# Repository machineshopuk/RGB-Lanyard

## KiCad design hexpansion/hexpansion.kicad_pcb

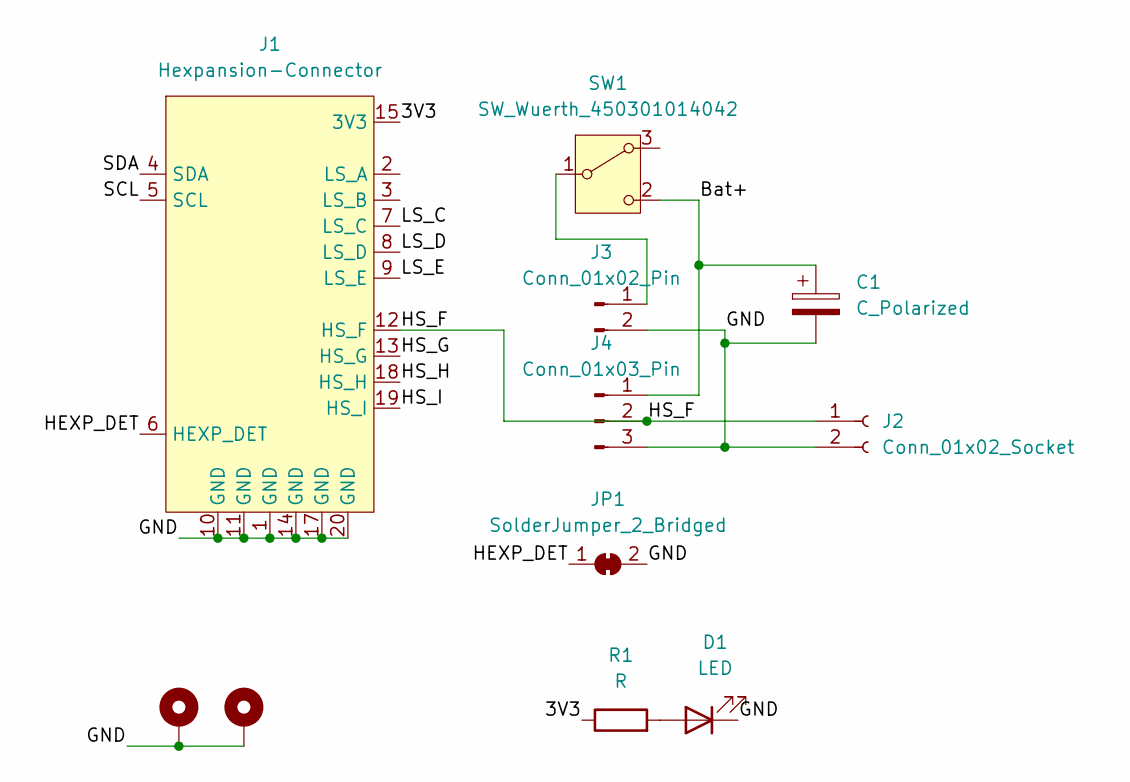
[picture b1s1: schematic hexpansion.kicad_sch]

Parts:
C1: C_Polarized; CP_Radial_D8.0mm_P3.50mm
D1: LED; LED_0805_2012Metric
H1, H2: MountingHole_Pad; MountingHole_2.2mm_M2_Pad_Via
J1: Hexpansion-Connector; hexpansion-edge-connector
J2: Conn_01x02_Socket; PinSocket_1x02_P2.54mm_Horizontal
J3: Conn_01x02_Pin; JST_XH_B2B-XH-A_1x02_P2.50mm_Vertical
J4: Conn_01x03_Pin; JST_XH_B3B-XH-A_1x03_P2.50mm_Vertical
JP1: SolderJumper_2_Bridged; SolderJumper-2_P1.3mm_Bridged_RoundedPad1.0x1.5mm
R1: R; R_0603_1608Metric
SW1: SW_Wuerth_450301014042; SW_Slide-03_Wuerth-WS-SLTV_10x2.5x6.4_P2.54mm

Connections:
/3V3: J1.15 (3V3), J1.16 (3V3), R1.1
/Bat+: C1.1, J4.1, SW1.2 (C)
/GND: C1.2, D1.1 (K), H1.1, H2.1, J1.1 (GND), J1.10 (GND), J1.11 (GND), J1.14 (GND), J1.17 (GND), J1.20 (GND), J2.2, J3.2, J4.3, JP1.2 (B)
/HEXP_DET: J1.6 (HEXP_DET), JP1.1 (A)
/HS_F: J1.12 (HS_F), J2.1, J4.2
/HS_G: J1.13 (HS_G)
/HS_H: J1.18 (HS_H)
/HS_I: J1.19 (HS_I)
/LS_C: J1.7 (LS_C)
/LS_D: J1.8 (LS_D)
/LS_E: J1.9 (LS_E)
/SCL: J1.5 (SCL)
/SDA: J1.4 (SDA)
unnamed: D1.2 (A), R1.2
unnamed: J3.1, SW1.1 (B)

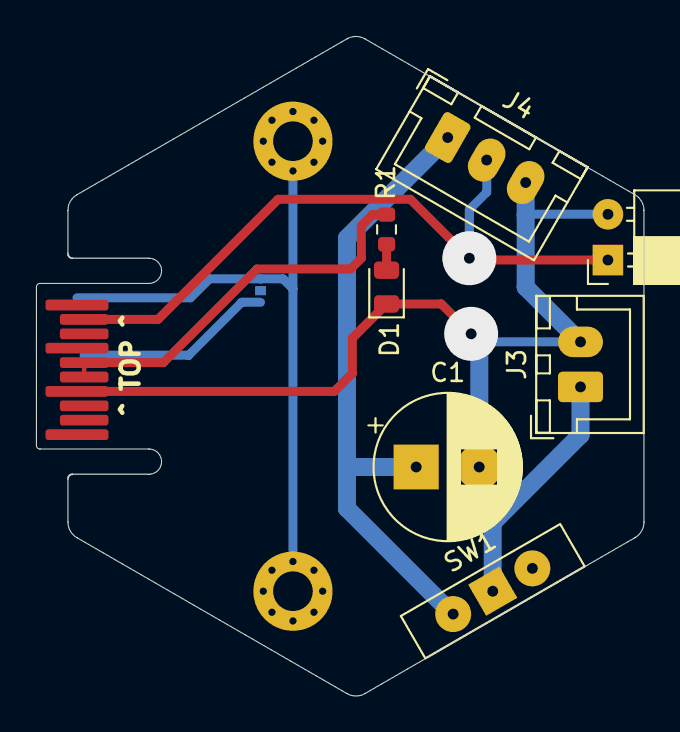
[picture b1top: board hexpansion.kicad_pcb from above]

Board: 2 copper layers, 33.7 x 36.6 mm, 11 parts (1 on the bottom side), 7 nets.
